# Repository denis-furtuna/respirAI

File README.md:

<picture>
  <source media="(prefers-color-scheme: dark)" srcset="docs/brand/logo-lockup-dark.png">
  
</picture>

**A low-cost digital stethoscope that guides the patient, listens to the lungs, and screens the sounds with AI.**

[Project plan](docs/PLAN.md) · [Architecture](docs/ARCHITECTURE.md) · [Enclosure](docs/ENCLOSURE.md) · [Add-ons](docs/ADDONS.md)

> [!IMPORTANT]
> respirAI is a student hackathon project, **not a medical device**. It does not diagnose and must not be used to make health decisions. If you are unwell, see a doctor.

## Overview

The stethoscope has barely changed since Laennec invented it in 1816, and interpreting what it hears still takes a trained ear.

respirAI answers one question: *do these lungs sound normal, or should you see a doctor?*

1. The phone shows a torso diagram marking where to place the chest piece.
2. The lungs printed on the device light up and pace the patient's breathing, in step with the circle on the phone. The phone shows where to place the chest piece; the device shows when to breathe.
3. The device records each chest position and streams the audio to the phone over Bluetooth.
4. A neural network screens each recording for **crackles** and **wheezes** and reports a per-position finding.

No clinical training is needed to take a recording.

## How it works

The device captures audio at 16 kHz, downsamples to 8 kHz and streams 10 ms packets over Bluetooth Low Energy. The phone reassembles them, guides the user through the seven ICBHI chest positions, and sends each recording for inference. Results come back as JSON and are shown per position.

The system is split along three fixed interfaces, so each part can be built independently:

| Interface | Contract |
|---|---|
| Firmware → App | BLE service `7b8c9d00-0001-…`, 162-byte packets: 2-byte sequence + 10 ms of 8 kHz 16-bit mono PCM |
| App → AI | `POST /analyze` with a WAV and a chest position code; returns `finding`, `confidence`, `quality` |
| Electronics → CAD | measured component dimensions in [`cad/components.csv`](cad/components.csv) |

Full specification: [`docs/ARCHITECTURE.md`](docs/ARCHITECTURE.md).

## Hardware

Everything is off the shelf. There is no custom PCB, and the whole device costs roughly 200 lei.

| Part | Role | |
|---|---|---|
| Seeed XIAO ESP32-S3 | MCU, Bluetooth, battery charging | core |
| INMP441 | I²S MEMS microphone | core |
| Stethoscope chest piece + tube | acoustic front end | core |
| LiPo 3.7 V 2500 mAh | power | core |
| 4 × LED behind a printed lung panel | breathing guide (trachea + two lobes) and "AI" status light | core |
| AD8232 | single-lead ECG | [add-on](docs/ADDONS.md) |
| MAX30102 | pulse and SpO2 | [add-on](docs/ADDONS.md) |

The add-ons are extensions to the same platform, which already provides the power, sensor bus and app pipeline. They are built only once the core is finished.

## The model

Trained on the **ICBHI 2017 Respiratory Sound Database** (920 recordings, 126 participants). It classifies each respiratory cycle as *normal*, *crackles*, *wheezes* or *both*.

- **Sound labels, not disease labels.** ICBHI's disease labels are ~86 % COPD, so a model trained on them scores well by always guessing one class.
- **Patient-wise splits, never random.** A random split puts the same patient in train and test and inflates accuracy.

Per-class results will be published here once training runs, with the split described.

## Repository

```
firmware/   ESP32: I²S capture, downsampling, BLE service, LED guide
app/        web app: Web Bluetooth, guided recording, results
ai/         preprocessing, training, inference server
cad/        enclosure models, print files, components.csv
docs/       plan, architecture, enclosure design, add-ons
```

## Status

Built for the **Medical Renaissance** hackathon in Timișoara. Hardware is on order.

| Part | State |
|---|---|
| Architecture and interface contracts | defined |
| Firmware | not started |
| Web app | not started |
| AI model | not started |
| Enclosure | not started |

## Team

| Name | Role |
|---|---|
| *TBD* | firmware, electronics |
| *TBD* | web app |
| *TBD* | AI / data |
| *TBD* | CAD, enclosure |

## Concept

<sub><i>Concept render. The real enclosure is designed only after the electronics are measured and frozen. See <a href="docs/ENCLOSURE.md">docs/ENCLOSURE.md</a>.</i></sub>

## License

[MIT](LICENSE)

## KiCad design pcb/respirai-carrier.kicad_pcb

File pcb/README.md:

# pcb/: the carrier board

One board that replaces the jumpers. It sits right under the lid, screwed onto the case's four corner posts: the four LEDs are on top, shining straight into the lung panel, and everything else hangs underneath. The modules you already have plug into it: the XIAO, the mic, and later the ECG and pulse sensors. No chips to solder, only through-hole parts.

| On the board | Side | Pins (firmware/respirai/config.h, docs/ADDONS.md) |
|---|---|---|
| XIAO ESP32-S3, USB-C to the left wall | bottom | — |
| 4 LEDs: trachea, two lobes, the "AI" of the wordmark | top | D6, D7 (both lobes, one resistor each), D3 |
| J2 mic plug, 6 pins: GND, 3V3, SD, WS, SCK, L/R (to GND) | bottom | D10, D9, D8 |
| J1 battery plug, J3 switch plug | bottom | through the switch to the XIAO's BAT+ |
| Battery level: 2 × 100 kΩ + 100 nF | bottom | D1 |
| J4 pulse (MAX30102): 3V3, GND, SDA, SCL | bottom | D4, D5 (add-on, can stay empty) |
| J5 ECG (AD8232): GND, 3V3, OUT, LO−, LO+, SDN | bottom | D0, D2 (add-on, can stay empty) |

All 11 of the XIAO's pins are used, as planned in `docs/ADDONS.md`. Its 5V pin stays unconnected: the board runs from the LiPo.

## Before ordering: three checks

1. **Print `fab/respirai-carrier-1to1-top.pdf` at 100 % (no "fit to page") and lay the parts on it.** The XIAO's pins must sit on its 14 holes, the LEDs on theirs, the plugs on theirs. Thirty seconds, and the most common PCB mistake is caught.
2. **The case designer agrees on the outline:** 95 × 80 mm, corner radius 6, centred in the 100 × 85 mm case; M3 holes on the case's four corner posts, 8 mm in from each wall's outer face (as in `docs/ENCLOSURE.md`). The board sits under the lid; below it hang the XIAO (≈ 13 mm in female headers, ≈ 7 mm soldered straight in) and the plugs (≈ 7 mm). Keep those clear of the battery and the mic pocket.
3. **The lung panel artwork matches the LEDs.** Centres, from the front-left corner seen from above: trachea X 50 / Y 58, lobes X 38 / Y 40 and X 62 / Y 40, "AI" X 66 / Y 7 (all mm). To move one, change its line in `generate.py` and rebuild.

## Order it (JLCPCB)

1. jlcpcb.com → *Order now* → *Add gerber file* → `fab/respirai-carrier-jlcpcb.zip`. It reads 2 layers and 95 × 80 mm by itself.
2. Leave the defaults: FR-4, 1.6 mm, 1 oz copper, HASL (lead-free if you like). Any colour; quantity 5 is the minimum and costs about the same as 1.
3. Shipping: DHL or FedEx express, about 4–6 days to Romania. Order by ~21 October and there are two weeks left for assembly and tests before 13 November.

No assembly service needed: everything is through-hole and hand-soldered.

## Parts

| Ref | Part | Qty |
|---|---|---|
| U1 | Seeed XIAO ESP32-S3 (you have it) + 2 × 1×7 female headers, 2.54 mm, to keep it removable | 1 |
| D1–D4 | 3 mm diffused LED (you have them). Long leg = anode = the round pad; short leg = the square pad | 4 |
| R1–R4 | 100 Ω, ¼ W axial (47 Ω for brighter, never lower) | 4 |
| R5, R6 | 100 kΩ, ¼ W axial | 2 |
| C1 | 100 nF ceramic, 2.5 mm pitch | 1 |
| J1, J3 | JST PH 2.0 mm, 2-pin, vertical (B2B-PH-K) | 2 |
| J4 | JST PH 2.0 mm, 4-pin, vertical (B4B-PH-K) | 1 |
| J2, J5 | JST PH 2.0 mm, 6-pin, vertical (B6B-PH-K) | 2 |
| cables | JST PH 2.0 pre-crimped leads with open ends: 2-pin × 1 (switch), 6-pin × 1 (mic), later 4-pin and 6-pin for the add-ons. A small JST PH kit covers it | — |

The LiPo (LP-785060) already ends in a JST PH 2.0 plug, so it goes straight into J1. **Measure its polarity first:** cheap LiPos wire the plug either way round. If its + doesn't land on the pin marked + on the board, swap the two crimps in the plug (lift the tab with a needle) — never plug in reversed, the XIAO has no protection.

## Assembly order

Lowest parts first, testing as you go with the module tests on the `firmware` branch:

1. **Resistors and C1** (bottom side, the row along the rear edge). The labels say which LED each one feeds.
2. **LEDs** from the top: long leg in the round pad. Leave them a little proud so they reach the panel.
3. **Plugs J1–J5** from the bottom.
4. **Two short wires** from the BAT+ / BAT− pads to the XIAO's BAT+ / BAT− pads (on its underside, BAT− nearer the USB-C). Solder these to the XIAO first, then mount it.
5. **The XIAO** in its female headers, USB-C towards the board edge marked on the silkscreen.
6. Test: `firmware/led_test` (each LED lights, `i`), `firmware/mic_test` (wiring check says OK), then the full firmware with the app. With the divider on the board, set `PIN_BATTERY = 2` in `config.h` so the app shows the battery level.

## Files

| File | What it is |
|---|---|
| `generate.py` | places every part, names every net, draws the outline and ground fills. **Change the board here**, not in KiCad |
| `route.py` | routes it with Freerouting and fills the ground planes |
| `check.py` | checks the result against the firmware's own pins (`config.h`), independently of how `generate.py` named things |
| `build.py` | all of the above + KiCad's DRC + the exports below; stops at the first failure |
| `respirai-carrier.kicad_pcb` | the routed board; opens in KiCad 10 |
| `respirai.pretty/` | the XIAO footprint, from Seeed's own (pins 15.24 mm apart, 2.54 mm pitch) |
| `fab/` | what to send and print: the Gerber zip for JLCPCB, 1:1 PDFs, renders |

Rebuild after any change (KiCad 10, Freerouting 2.x and the Java it needs):

```bash
JAVA=path/to/java FREEROUTING_JAR=path/to/freerouting-2.4.1.jar python pcb/build.py
```

The last build: every connection routed (2 vias), KiCad DRC with all severities: 0 violations, 0 unconnected; `check.py`: all 46 checks pass.

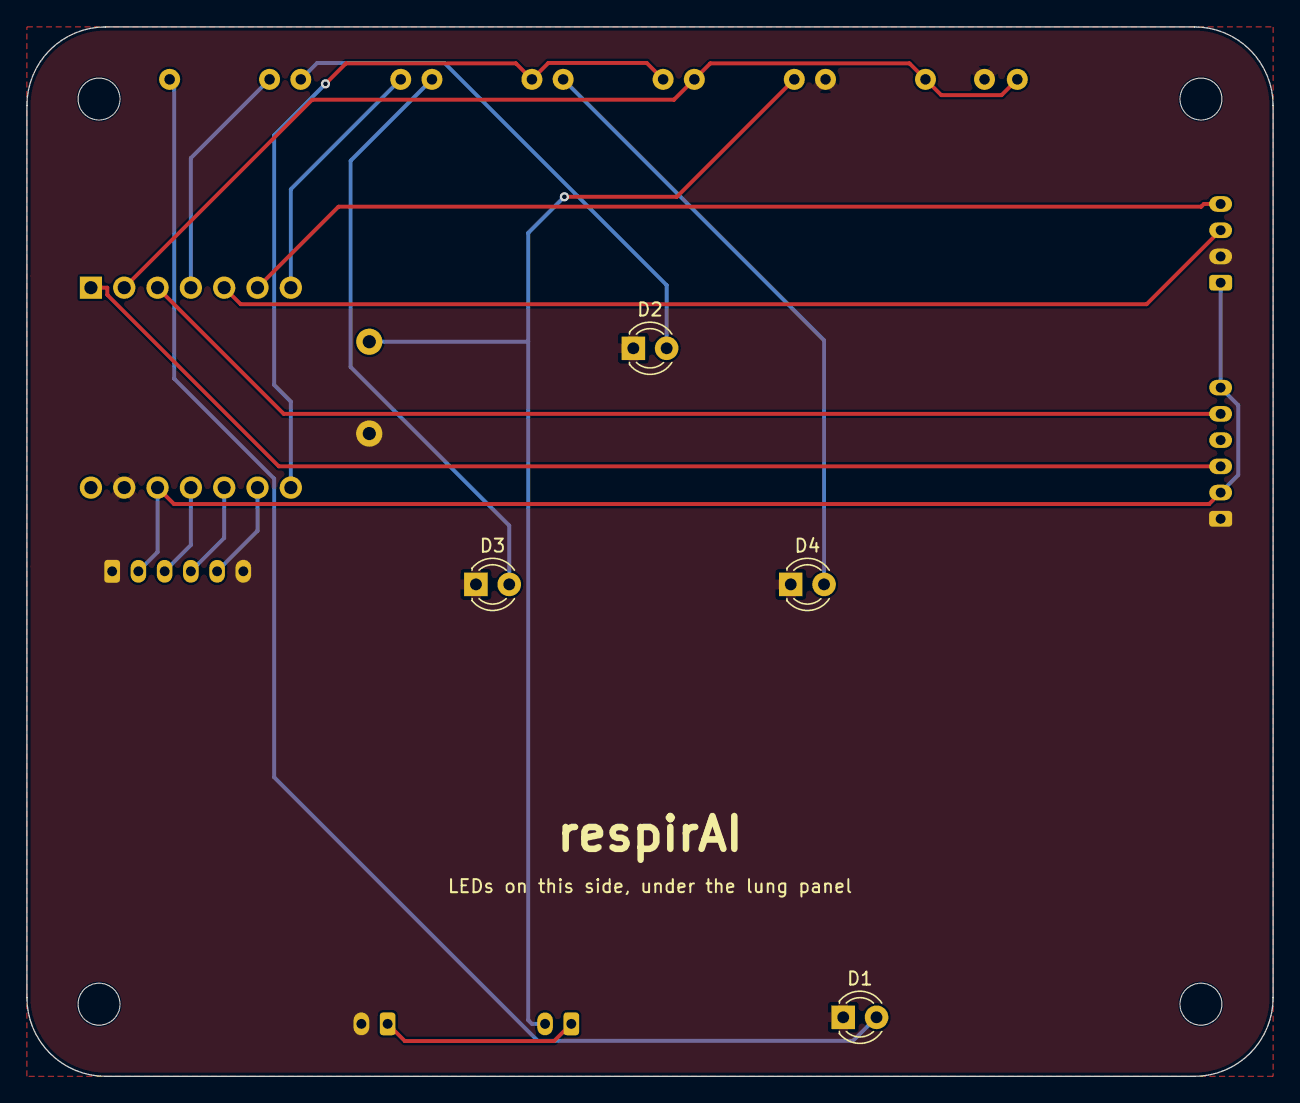
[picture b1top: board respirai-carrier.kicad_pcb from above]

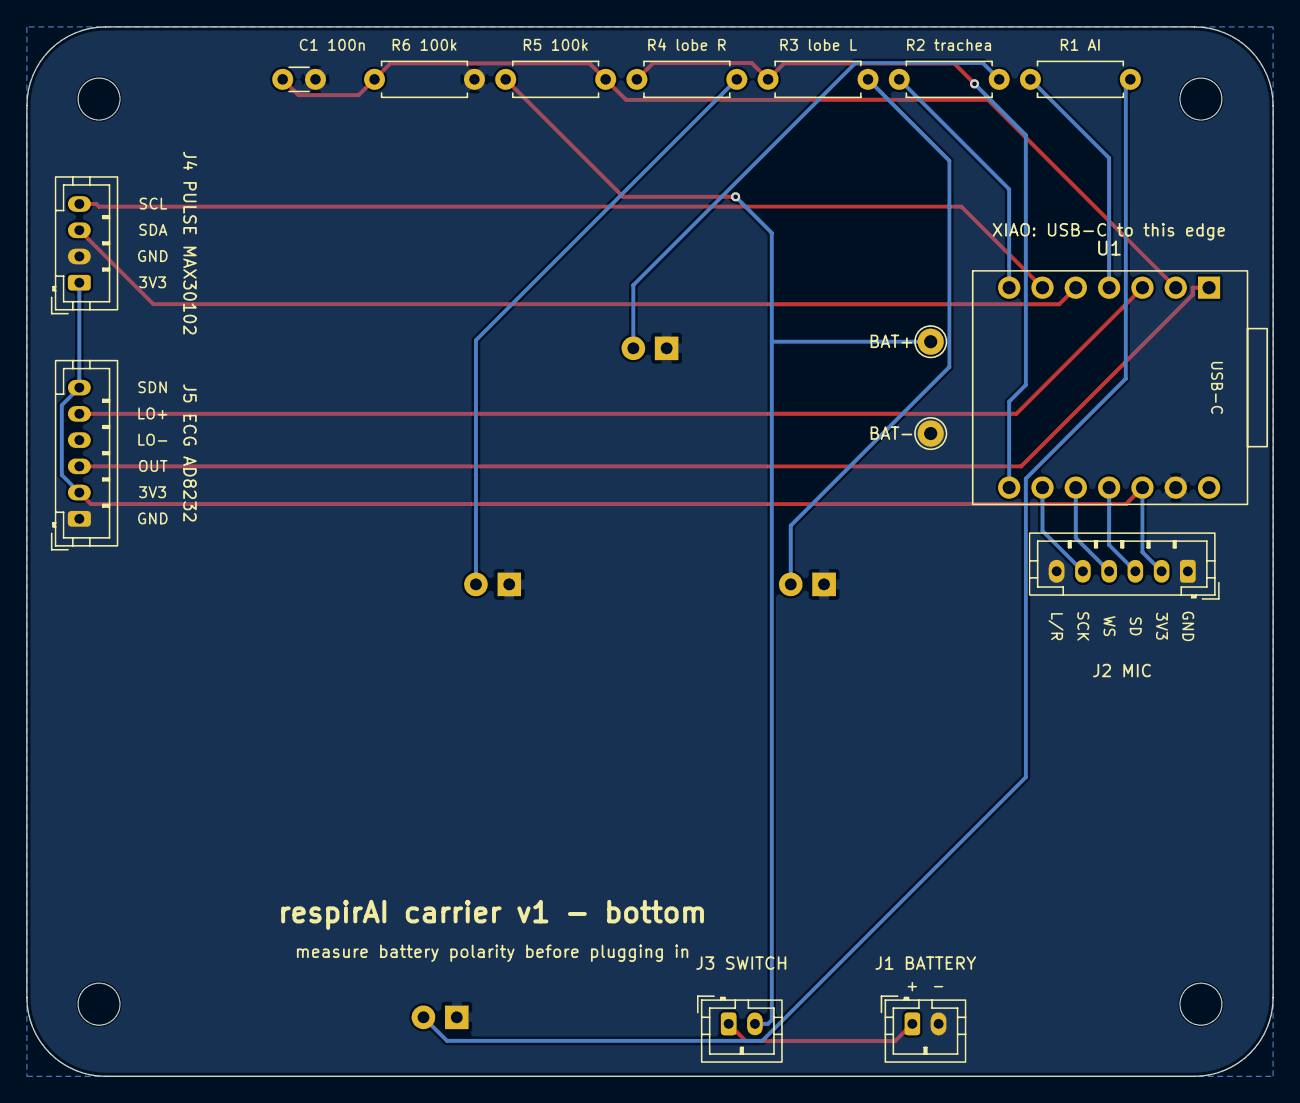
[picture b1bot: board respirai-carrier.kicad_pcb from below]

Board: 2 copper layers, 95.0 x 80.0 mm, 23 parts (15 on the bottom side), 19 nets.

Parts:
C1: 100n; C_Disc_D3.0mm_W1.6mm_P2.50mm
D1: AI; LED_D3.0mm
D2: trachea; LED_D3.0mm
D3: lobe L; LED_D3.0mm
D4: lobe R; LED_D3.0mm
H1, H2, H3, H4: M3; MountingHole_3.2mm_M3
J1: BATTERY; JST_PH_B2B-PH-K_1x02_P2.00mm_Vertical
J2: MIC; JST_PH_B6B-PH-K_1x06_P2.00mm_Vertical
J3: SWITCH; JST_PH_B2B-PH-K_1x02_P2.00mm_Vertical
J4: PULSE; JST_PH_B4B-PH-K_1x04_P2.00mm_Vertical
J5: ECG; JST_PH_B6B-PH-K_1x06_P2.00mm_Vertical
R1, R2, R3, R4: 100; R_Axial_DIN0207_L6.3mm_D2.5mm_P7.62mm_Horizontal
R5, R6: 100k; R_Axial_DIN0207_L6.3mm_D2.5mm_P7.62mm_Horizontal
TP1: BAT+; TestPoint_THTPad_D2.0mm_Drill1.0mm
TP2: BAT-; TestPoint_THTPad_D2.0mm_Drill1.0mm
U1: XIAO ESP32-S3; XIAO_ESP32S3_THT

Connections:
3V3: J2.2, J4.1, J5.2, J5.6, U1.12
AI_A: D1.2, R1.2
BAT_SENSE: C1.1, R5.2, R6.1, U1.2
ECG_LO+: J5.5, U1.3
ECG_OUT: J5.3, U1.1
GND: C1.2, D1.1, D2.1, D3.1, D4.1, J1.2, J2.1, J2.6, J4.2, J5.1, R6.2, TP2.1, U1.13
I2C_SCL: J4.4, U1.6
I2C_SDA: J4.3, U1.5
LED_AI: R1.1, U1.4
LED_LOBES: R3.1, R4.1, U1.8
LED_TRACHEA: R2.1, U1.7
LOBE_L_A: D3.2, R3.2
LOBE_R_A: D4.2, R4.2
MIC_SCK: J2.5, U1.9
MIC_SD: J2.3, U1.11
MIC_WS: J2.4, U1.10
TRACHEA_A: D2.2, R2.2
VBAT: J3.2, R5.1, TP1.1
VBAT_IN: J1.1, J3.1

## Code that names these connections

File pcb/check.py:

"""Checks the routed board against what the firmware expects, independently of how generate.py named the nets.

    D:/KiCad/bin/python.exe pcb/check.py

DRC proves the copper matches the board's own netlist; this proves the netlist is the right circuit: every XIAO pin
reaches the part the firmware (firmware/respirai/config.h) and docs/ADDONS.md say it drives. Exits 1 on any mismatch.
"""
import re
import sys
from pathlib import Path

import pcbnew

HERE = Path(__file__).resolve().parent
ROOT = HERE.parent
board = pcbnew.LoadBoard(str(HERE / "respirai-carrier.kicad_pcb"))
problems = []


def pads_on(netname):
    return {(p.GetParentFootprint().GetReference(), p.GetNumber()) for p in board.GetPads() if p.GetNetname() == netname}


def net_of(ref, pad):
    p = board.FindFootprintByReference(ref).FindPadByNumber(pad)
    return p.GetNetname()


def expect(what, ok):
    print(("ok    " if ok else "WRONG ") + what)
    if not ok:
        problems.append(what)


# XIAO pin numbers -> D-names (Seeed's XIAO-ESP32-S3 symbol) and D-name -> GPIO (the XIAO ESP32-S3 pinout)
XIAO_PIN = {f"D{i}": str(i + 1) for i in range(11)} | {"3V3": "12", "GND": "13"}
GPIO = {"D0": 1, "D1": 2, "D2": 3, "D3": 4, "D4": 5, "D5": 6, "D6": 43, "D7": 44, "D8": 7, "D9": 8, "D10": 9}

# What the firmware drives, read from config.h itself (so a pin change there shows up here)
cfg = (ROOT / "firmware" / "respirai" / "config.h").read_text(encoding="utf-8") if (ROOT / "firmware").exists() else ""
fw = {k: int(v) for k, v in re.findall(r"constexpr int (PIN_\w+)\s*=\s*(-?\d+)", cfg)}
by_gpio = {g: d for d, g in GPIO.items()}
if fw:
    for name, gpio in fw.items():
        if gpio >= 0:
            print(f"      config.h {name} = GPIO {gpio} = {by_gpio.get(gpio, '?')}")

# The circuit, as (XIAO D-pin, the other end it must reach)
want = [
    ("D8", ("J2", "5"), "mic SCK"), ("D9", ("J2", "4"), "mic WS"), ("D10", ("J2", "3"), "mic SD"),
    ("D3", ("R1", "1"), "AI LED resistor"), ("D6", ("R2", "1"), "trachea LED resistor"),
    ("D7", ("R3", "1"), "left lobe resistor"), ("D7", ("R4", "1"), "right lobe resistor"),
    ("D1", ("R5", "2"), "battery divider"), ("D0", ("J5", "3"), "ECG OUT"), ("D2", ("J5", "5"), "ECG LO+"),
    ("D4", ("J4", "3"), "pulse SDA"), ("D5", ("J4", "4"), "pulse SCL"),
]
for d, (ref, pad), what in want:
    expect(f"{d} -> {ref}.{pad} ({what})", (ref, pad) in pads_on(net_of("U1", XIAO_PIN[d])))

# The firmware's own pins land where this board puts them
if fw:
    for key, d in [("PIN_MIC_SCK", "D8"), ("PIN_MIC_WS", "D9"), ("PIN_MIC_SD", "D10"), ("PIN_LED_AI", "D3"),
                   ("PIN_LED_TRACHEA", "D6"), ("PIN_LED_LOBES", "D7")]:
        expect(f"config.h {key} is {d} (GPIO {GPIO[d]})", fw.get(key) == GPIO[d])

# Each resistor feeds the right LED's anode (pad 2 = anode); every LED cathode and the mic's L/R go to ground
for r, led in [("R1", "D1"), ("R2", "D2"), ("R3", "D3"), ("R4", "D4")]:
    expect(f"{r} -> {led} anode", (led, "2") in pads_on(net_of(r, "2")))
    expect(f"{led} cathode on GND", net_of(led, "1") == "GND")
gnd = pads_on("GND")
for ref, pad, what in [("J2", "1", "mic GND"), ("J2", "6", "mic L/R"), ("U1", "13", "XIAO GND"), ("TP2", "1", "BAT-"),
                       ("J1", "2", "battery -"), ("J4", "2", "pulse GND"), ("J5", "1", "ECG GND"), ("R6", "2", "divider"),
                       ("C1", "2", "divider cap")]:
    expect(f"{ref}.{pad} on GND ({what})", (ref, pad) in gnd)
v33 = pads_on(net_of("U1", "12"))
for ref, pad, what in [("J2", "2", "mic VDD"), ("J4", "1", "pulse VIN"), ("J5", "2", "ECG 3V3"), ("J5", "6", "ECG SDN high")]:
    expect(f"{ref}.{pad} on 3V3 ({what})", (ref, pad) in v33)

# Power path: battery + -> switch -> BAT+ pad and divider top; 5V pin unused
expect("battery + -> switch", ("J3", "1") in pads_on(net_of("J1", "1")))
expect("switch -> BAT+ pad", ("TP1", "1") in pads_on(net_of("J3", "2")))
expect("switch -> divider top", ("R5", "1") in pads_on(net_of("J3", "2")))
expect("battery never reaches 3V3 or a GPIO directly", net_of("J1", "1") not in {net_of("U1", str(i)) for i in range(1, 13)})
expect("XIAO 5V pin left unconnected", net_of("U1", "14") == "")

# Every net with a name reaches at least two pads, and the copper really connects them
conn = board.GetConnectivity()
conn.RecalculateRatsnest()
expect("no unrouted connections", conn.GetUnconnectedCount(True) == 0)
for n in {p.GetNetname() for p in board.GetPads() if p.GetNetname()}:
    expect(f"net {n} has 2+ pads", len(pads_on(n)) >= 2) if len(pads_on(n)) < 2 else None

print(f"\n{'ALL GOOD' if not problems else f'{len(problems)} PROBLEMS'}")
sys.exit(1 if problems else 0)
